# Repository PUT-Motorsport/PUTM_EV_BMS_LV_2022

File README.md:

# PUTM_EV_BMS_LV

## About
Battery Management System (BMS) is an electronic system that manages a rechargeable battery. In case of this project, it will be battery made of 21700 cells packed in 6S2P configuration.

## Tasks of Battery Management System:
- Voltage Measurement on every cell
- Current Measurement
- Temperature Measurement
- State of Charge calculate
- Charge Management with Cell Balance System
- Error Handling based on FSG Rules
- CAN - CAR communication
- Serial data print through USB

## Block diagram of the firmware

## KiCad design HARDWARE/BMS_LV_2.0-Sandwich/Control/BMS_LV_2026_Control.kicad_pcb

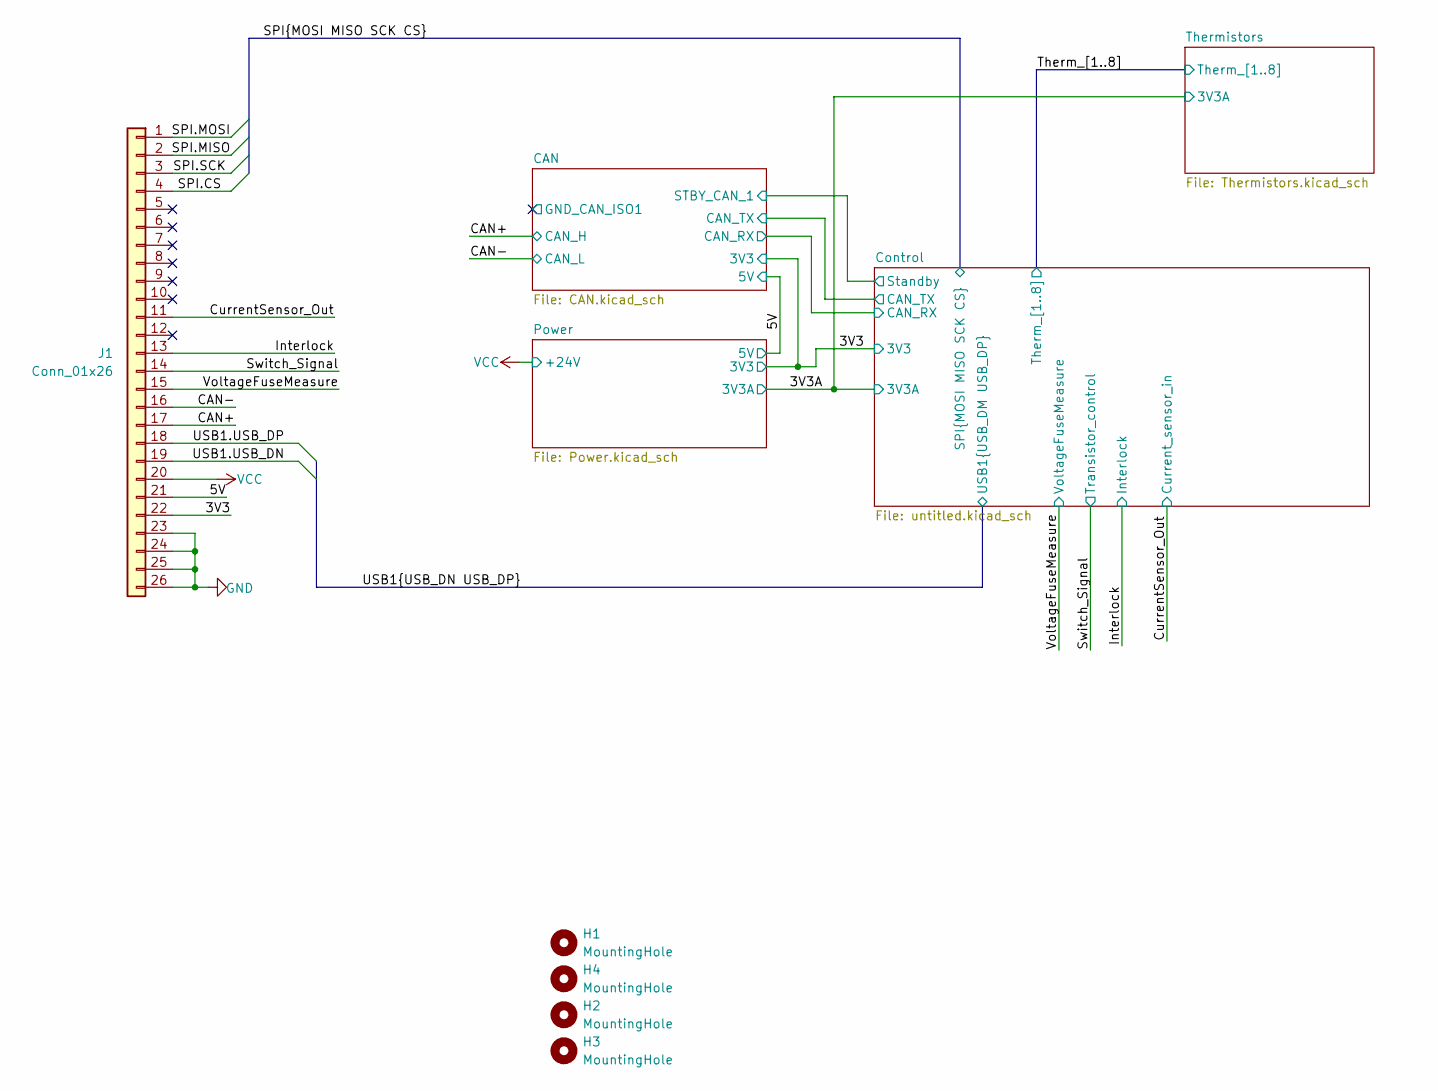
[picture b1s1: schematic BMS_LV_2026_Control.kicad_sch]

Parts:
H1, H2, H3, H4: MountingHole; MountingHole_2.2mm_M2
J1: Conn_01x26; M557002642R; Mouser Part Number M55-6002642R

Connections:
/3V3: J1.22; also elsewhere on the board
/5V: J1.21; also elsewhere on the board
/CAN+: J1.17; also elsewhere on the board
/CAN-: J1.16; also elsewhere on the board
/CurrentSensor_Out: J1.11; also elsewhere on the board
/Interlock: J1.13; also elsewhere on the board
/SPI.CS: J1.4; also elsewhere on the board
/SPI.MISO: J1.2; also elsewhere on the board
/SPI.MOSI: J1.1; also elsewhere on the board
/SPI.SCK: J1.3; also elsewhere on the board
/Switch_Signal: J1.14; also elsewhere on the board
/USB1.USB_DN: J1.19; also elsewhere on the board
/USB1.USB_DP: J1.18; also elsewhere on the board
/VoltageFuseMeasure: J1.15; also elsewhere on the board
GND: J1.23, J1.24, J1.25, J1.26; also elsewhere on the board
VCC: J1.20; also elsewhere on the board

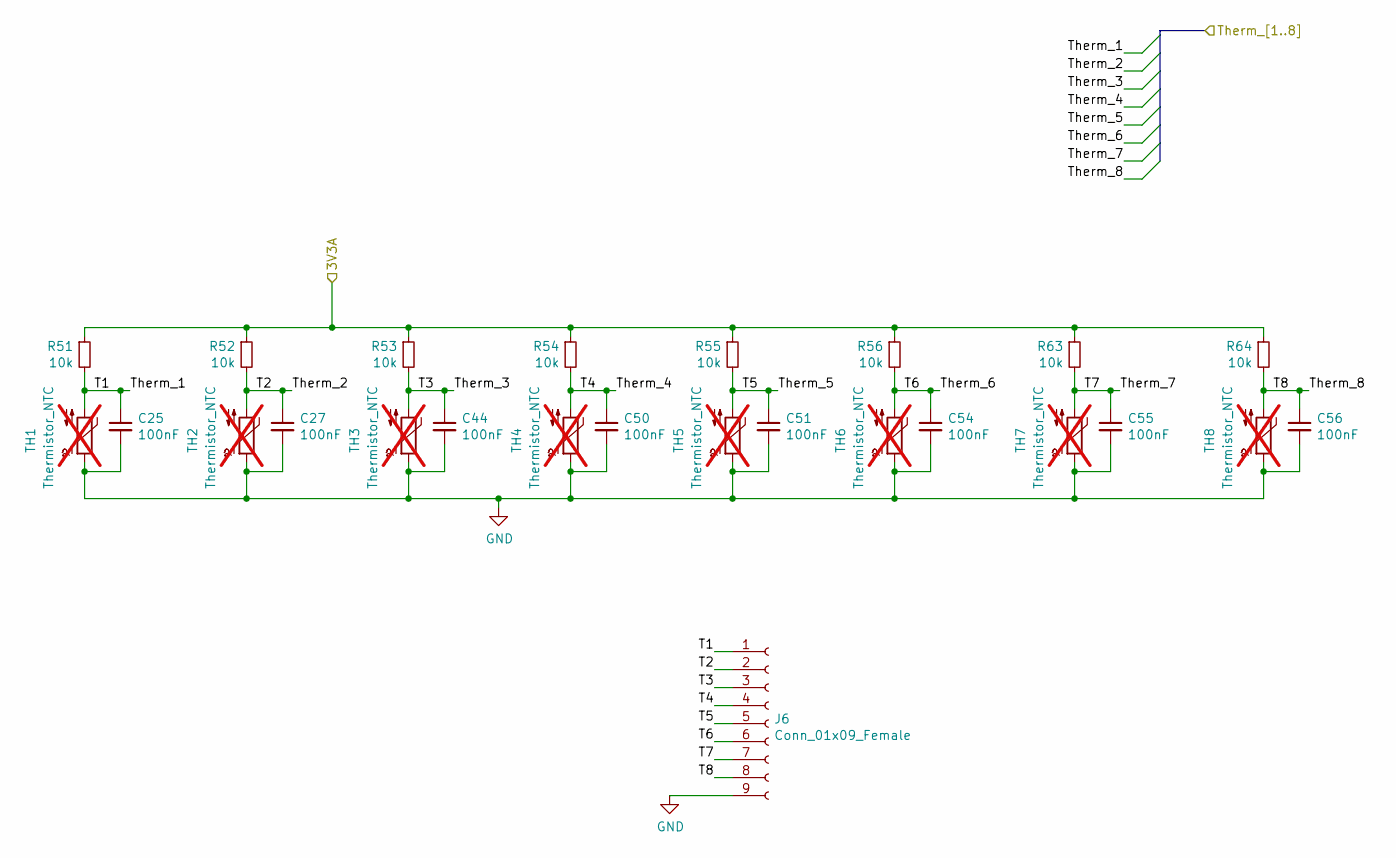
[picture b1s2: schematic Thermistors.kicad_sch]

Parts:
C25, C27, C44, C50, C51, C54, C55, C56: 100nF; C_0603_1608Metric
J6: Conn_01x09_Female; S9BXHA1LFSN
R51, R52, R53, R54, R55, R56, R63, R64: 10k; R_0603_1608Metric
TH1, TH2, TH3, TH4, TH5, TH6, TH7, TH8: Thermistor_NTC; not fitted

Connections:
/3V3A: R51.1, R52.1, R53.1, R54.1, R55.1, R56.1, R63.1, R64.1; also elsewhere on the board
/Therm_1: C25.1, J6.1, R51.2, TH1.2; also elsewhere on the board
/Therm_2: C27.1, J6.2, R52.2, TH2.2; also elsewhere on the board
/Therm_3: C44.1, J6.3, R53.2, TH3.2; also elsewhere on the board
/Therm_4: C50.1, J6.4, R54.2, TH4.2; also elsewhere on the board
/Therm_5: C51.1, J6.5, R55.2, TH5.2; also elsewhere on the board
/Therm_6: C54.1, J6.6, R56.2, TH6.2; also elsewhere on the board
/Therm_7: C55.1, J6.7, R63.2, TH7.2; also elsewhere on the board
/Therm_8: C56.1, J6.8, R64.2, TH8.2; also elsewhere on the board
GND: C25.2, C27.2, C44.2, C50.2, C51.2, C54.2, C55.2, C56.2, J6.9, TH1.1, TH2.1, TH3.1, TH4.1, TH5.1, TH6.1, TH7.1, TH8.1; also elsewhere on the board

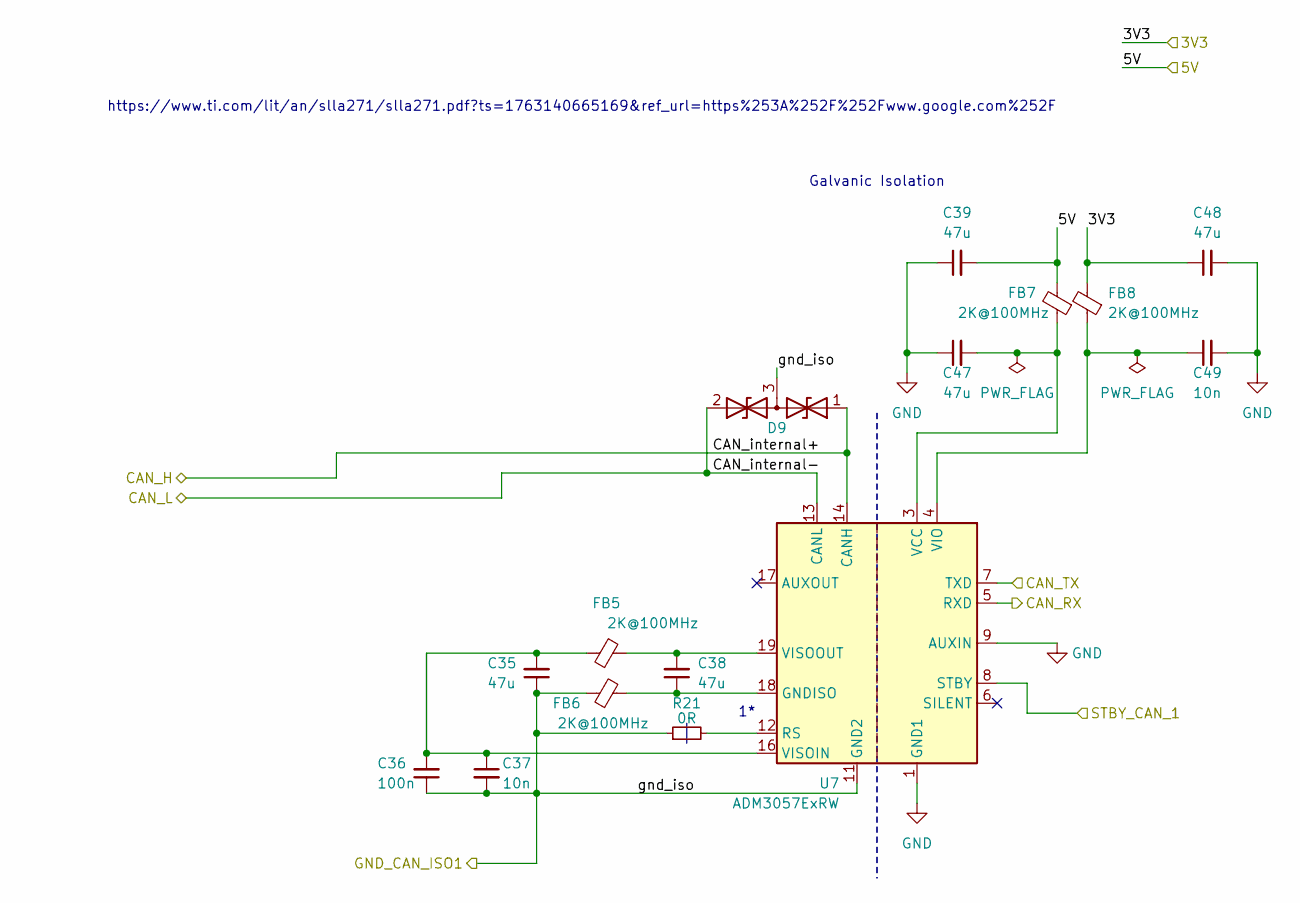
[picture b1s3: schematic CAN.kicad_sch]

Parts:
C35, C38, C39, C47, C48: 47u; C_0805_2012Metric_Pad1.18x1.45mm_HandSolder
C36: 100n; C_0603_1608Metric_Pad1.08x0.95mm_HandSolder
C37, C49: 10n; C_0603_1608Metric_Pad1.08x0.95mm_HandSolder
D9: D_TVS_Dual_AAC; SOT-23_Handsoldering
FB5, FB6, FB7, FB8: 2K@100MHz; L_0805_2012Metric_Pad1.05x1.20mm_HandSolder
R21: 0R; R_0603_1608Metric_Pad0.98x0.95mm_HandSolder
U7: ADM3057ExRW; SOIC-20W_7.5x12.8mm_P1.27mm

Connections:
/3V3: C48.1, FB8.2; also elsewhere on the board
/5V: C39.2, FB7.2; also elsewhere on the board
/CAN+: D9.1 (A1), U7.14 (CANH); also elsewhere on the board
/CAN-: D9.2 (A2), U7.13 (CANL); also elsewhere on the board
/CAN/CAN_RX: U7.5 (RXD); also elsewhere on the board
/CAN/CAN_TX: U7.7 (TXD); also elsewhere on the board
/CAN/STBY_CAN_1: U7.8 (STBY); also elsewhere on the board
/CAN/gnd_iso: C35.1, C36.1, C37.2, D9.3 (common), FB6.1, R21.1, U7.11 (GND2), U7.15 (GND2)
GND: C39.1, C47.1, C48.2, C49.2, U7.1 (GND1), U7.2 (GND1), U7.9 (AUXIN), U7.10 (GND1); also elsewhere on the board
unnamed: C38.1, FB6.2, U7.18 (GNDISO), U7.20 (GNDISO)
unnamed: R21.2, U7.12 (RS)
unnamed: C47.2, FB7.1, U7.3 (VCC)
unnamed: C49.1, FB8.1, U7.4 (VIO)
unnamed: C35.2, C36.2, C37.1, FB5.1, U7.16 (VISOIN)
unnamed: C38.2, FB5.2, U7.19 (VISOOUT)

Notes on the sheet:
https://www.ti.com/lit/an/slla271/slla271.pdf?ts=1763140665169&ref_url=https%253A%252F%252Fwww.google.com%252F
Galvanic Isolation

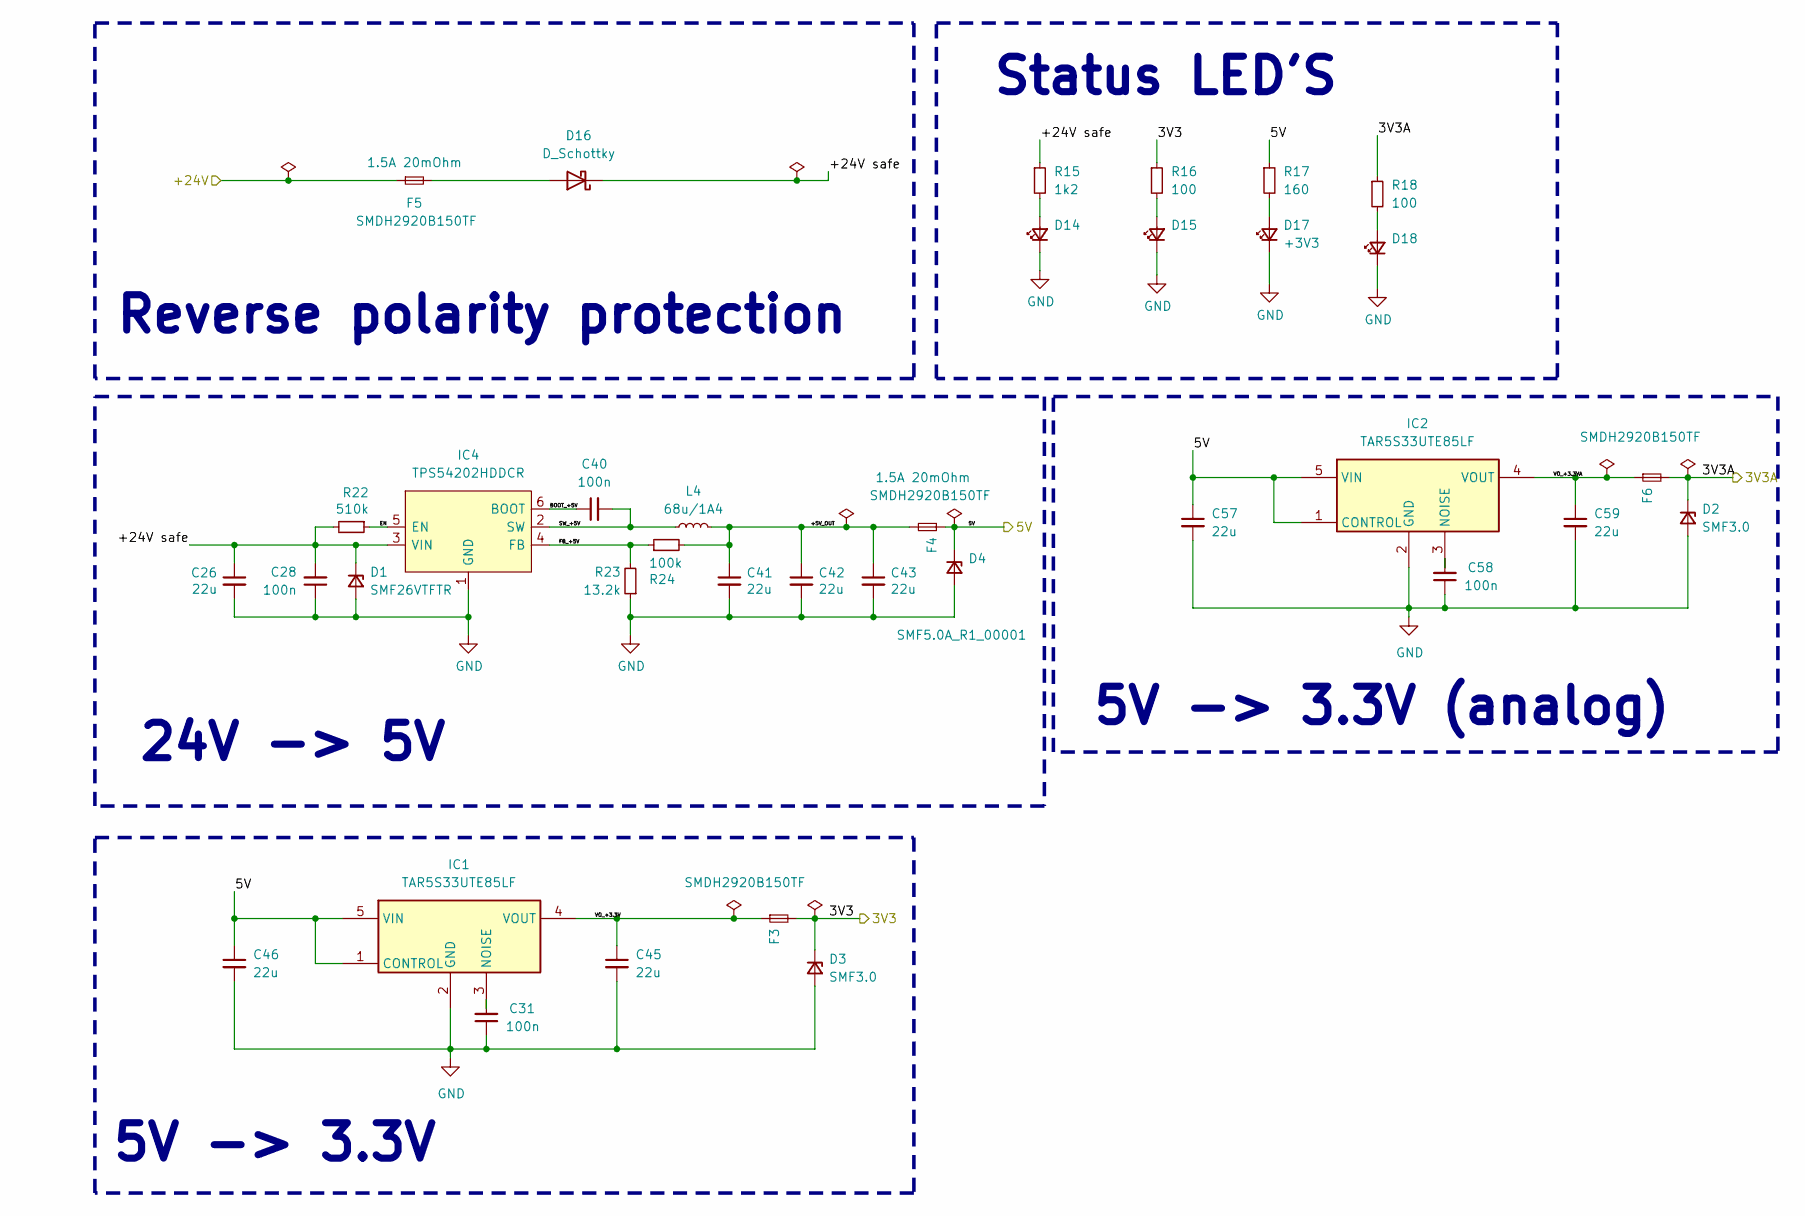
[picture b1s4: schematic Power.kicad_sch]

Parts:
C26, C41, C42, C43: 22u; C_0805_2012Metric_Pad1.18x1.45mm_HandSolder; Manufacturer_Part_Number CL21A107MQYNNWE; Mouser Part Number 810-C2012X5R1V226MAC
C28: 100n; C_0603_1608Metric_Pad1.08x0.95mm_HandSolder; Manufacturer_Part_Number C0603C104J3RACTU; Mouser Part Number 80-C0603C104J3R
C31, C58: 100n; C_0603_1608Metric; Manufacturer_Part_Number C0603C104J3RACTU; Mouser Part Number 80-C0603C104J3R
C40: 100n; C_0603_1608Metric_Pad1.08x0.95mm_HandSolder
C45, C46, C57, C59: 22u; C_0805_2012Metric_Pad1.18x1.45mm_HandSolder
D1: SMF26VTFTR; D_SOD-123F
D2, D3: SMF3.0; D_SOD-123F
D4: SMF5.0A_R1_00001; D_SOD-123F
D14, D15, D18: LED_0603_1608Metric_Pad1.05x0.95mm_HandSolder
D16: D_Schottky; D_0603_1608Metric_Pad1.05x0.95mm_HandSolder
D17: +3V3; LED_0603_1608Metric_Pad1.05x0.95mm_HandSolder
F3, F4, F5, F6: SMDH2920B150TF; Fuse_2920_7451Metric_Pad2.10x5.45mm_HandSolder
IC1, IC2: TAR5S33UTE85LF; SOTFL65P210X75-5N; Mouser Part Number 757-TAR5S33UTE85LF
IC4: TPS54202HDDCR; SOT-23-6_Handsoldering; Mouser Part Number 595-TPS54202HDDCR
L4: 68u/1A4; L_Vishay_IFSC-1515AH_4x4x1.8mm; Mouser Part Number 810-VLS6045EX-680M
R15: 1k2; R_0603_1608Metric_Pad0.98x0.95mm_HandSolder
R16, R18: 100; R_0603_1608Metric_Pad0.98x0.95mm_HandSolder
R17: 160; R_0603_1608Metric_Pad0.98x0.95mm_HandSolder
R22: 510k; R_0603_1608Metric_Pad0.98x0.95mm_HandSolder; Manufacturer_Part_Number RT0603DRD07510KL; Mouser Part Number 603-RT0603DRD07510KL
R23: 13.2k; R_0603_1608Metric_Pad0.98x0.95mm_HandSolder; Manufacturer_Part_Number RT0603DRE0713K3L; Mouser Part Number 603-RT0603DRE0713K3L
R24: 100k; R_0603_1608Metric_Pad0.98x0.95mm_HandSolder; Manufacturer_Part_Number RT0603DRE07100KL; Mouser Part Number 603-RT0603DRE07100KL

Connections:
/3V3: D3.1 (K), F3.2, R16.1; also elsewhere on the board
/3V3A: D2.1 (K), F6.2, R18.1; also elsewhere on the board
/5V: C46.1, C57.1, D4.1 (K), F4.1, IC1.1 (CONTROL), IC1.5 (VIN), IC2.1 (CONTROL), IC2.5 (VIN), R17.1; also elsewhere on the board
/Power/+5V_OUT: C41.1, C42.1, C43.1, F4.2, L4.2, R24.2
/Power/+24V safe: C26.1, C28.2, D1.1 (K), D16.1 (K), IC4.3 (VIN), R15.1, R22.2
/Power/BOOT_+5V: C40.1, IC4.6 (BOOT)
/Power/EN: IC4.5 (EN), R22.1
/Power/FB_+5V: IC4.4 (FB), R23.2, R24.1
/Power/SW_+5V: C40.2, IC4.2 (SW), L4.1
/Power/VO_+3.3V: C45.1, F3.1, IC1.4 (VOUT)
/Power/VO_+3.3VA: C59.1, F6.1, IC2.4 (VOUT)
GND: C26.2, C28.1, C31.1, C41.2, C42.2, C43.2, C45.2, C46.2, C57.2, C58.1, C59.2, D1.2 (A), D2.2 (A), D3.2 (A), D4.2 (A), D14.1 (K), D15.1 (K), D17.1 (K), D18.1 (K), IC1.2 (GND), IC2.2 (GND), IC4.1 (GND), R23.1; also elsewhere on the board
unnamed: D14.2 (A), R15.2
unnamed: D15.2 (A), R16.2
unnamed: D16.2 (A), F5.2
unnamed: D17.2 (A), R17.2
unnamed: D18.2 (A), R18.2
unnamed: C31.2, IC1.3 (NOISE)
unnamed: C58.2, IC2.3 (NOISE)
VCC: F5.1; also elsewhere on the board

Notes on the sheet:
Status LED'S
5V -> 3.3V (analog)
Reverse polarity protection
24V -> 5V
5V -> 3.3V

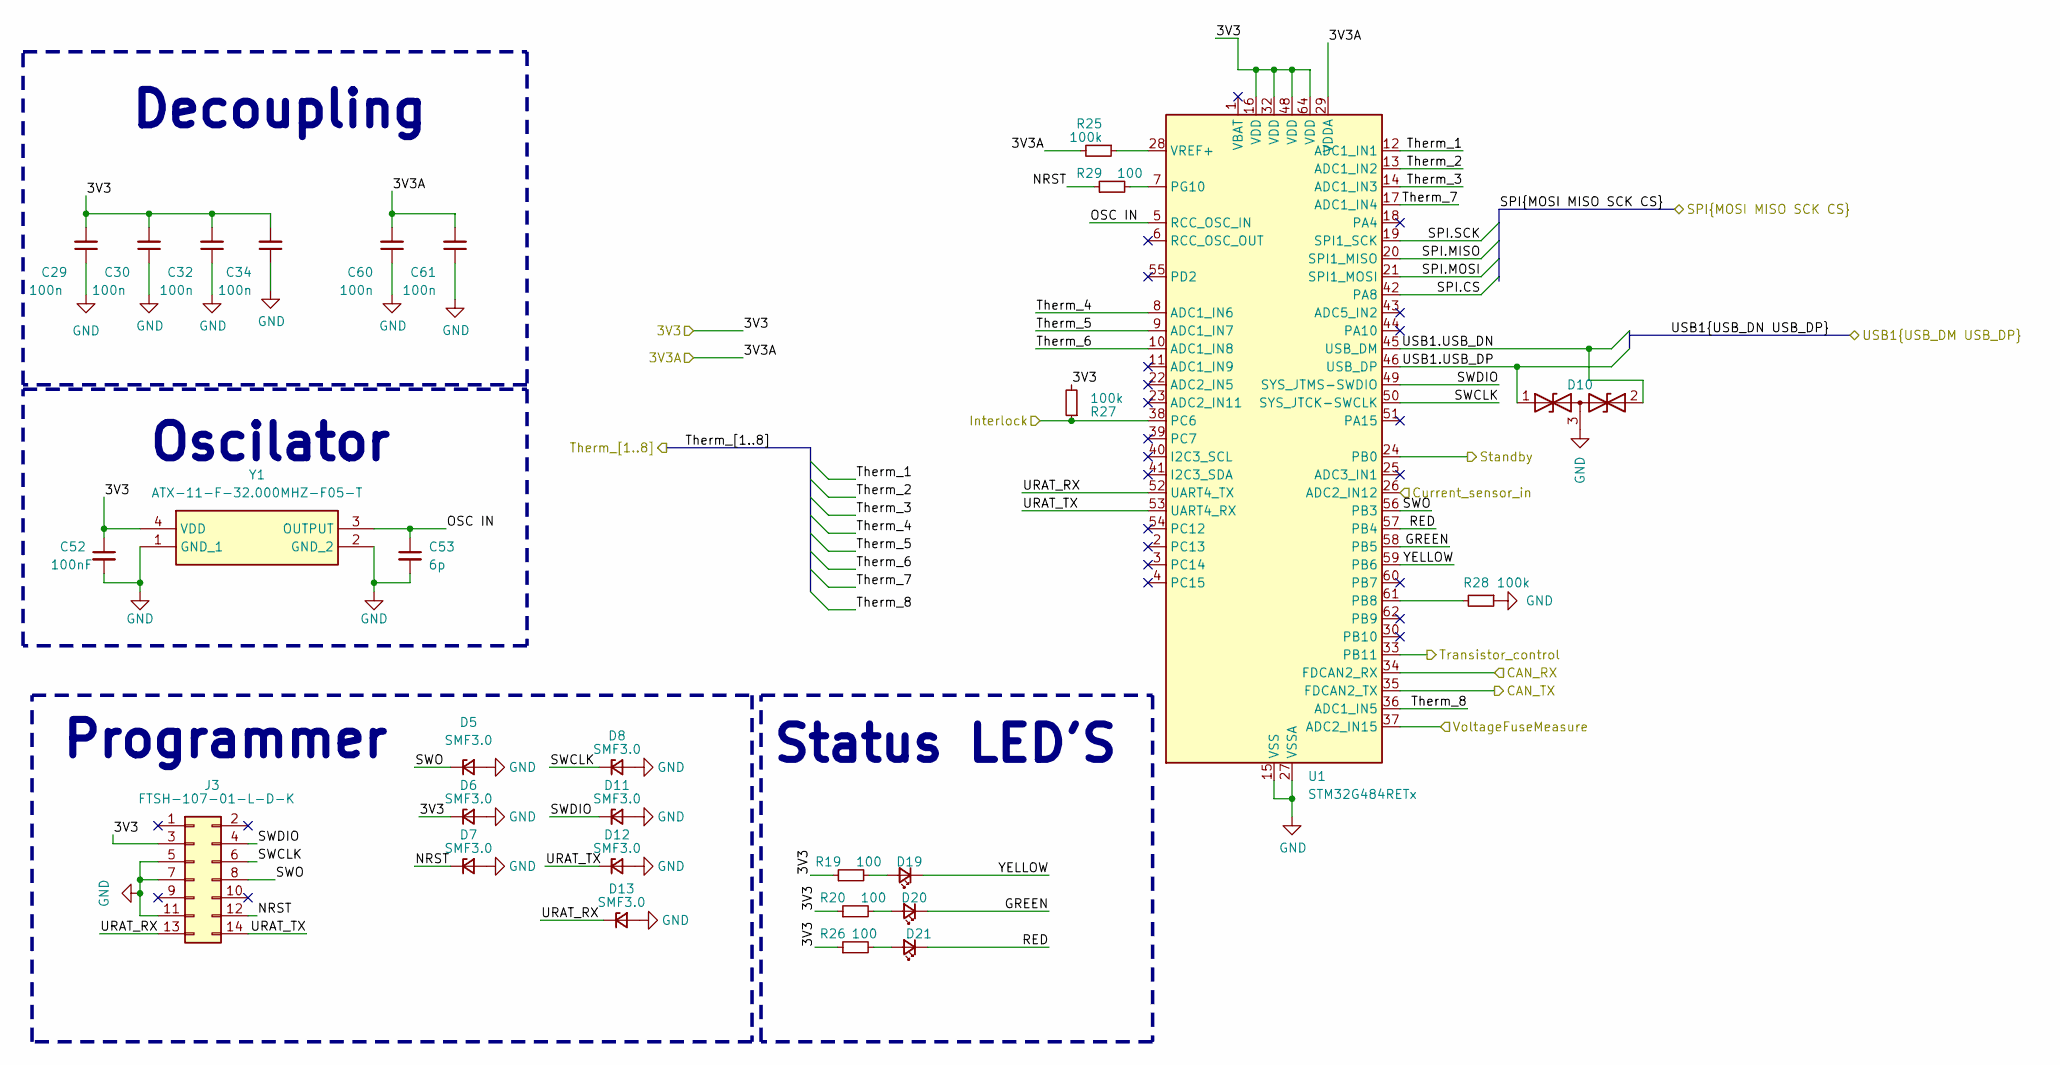
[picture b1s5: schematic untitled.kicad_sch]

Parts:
C29, C30, C32, C34, C60, C61: 100n; C_0603_1608Metric_Pad1.08x0.95mm_HandSolder; Manufacturer_Part_Number C0603C104J3RACTU; Mouser Part Number 80-C0603C104J3R
C52: 100nF; C_0603_1608Metric_Pad1.08x0.95mm_HandSolder
C53: 6p; C_0603_1608Metric_Pad1.08x0.95mm_HandSolder
D5, D6, D7, D8, D11, D12, D13: SMF3.0; D_SOD-123F
D10: D_TVS_Dual_AAC; SOT-23_Handsoldering
D19, D20, D21: LED_0603_1608Metric_Pad1.05x0.95mm_HandSolder
J3: FTSH-107-01-L-D-K; FTSH-107-XX-YYY-DH-TR; Mouser Part Number 200-FTSH10701LDK
R19, R20, R26, R29: 100; R_0603_1608Metric_Pad0.98x0.95mm_HandSolder
R25, R28: 100k; R_0603_1608Metric_Pad0.98x0.95mm_HandSolder
R27: 100k; R_0603_1608Metric_Pad0.98x0.95mm_HandSolder; Manufacturer_Part_Number RT0603DRE07100KL; Mouser Part Number 603-RT0603DRE07100KL
U1: STM32G484RETx; LQFP-64_10x10mm_P0.5mm
Y1: ATX-11-F-32.000MHZ-F05-T; ATX11F32000MHZF05T; Mouser Part Number 815-ATX11F32000MF05T

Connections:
/3V3: C29.2, C30.2, C32.2, C34.2, C52.1, D6.1 (K), J3.3, R19.1, R20.1, R26.1, R27.2, U1.16 (VDD), U1.32 (VDD), U1.48 (VDD), U1.64 (VDD), Y1.4 (VDD); also elsewhere on the board
/3V3A: C60.2, C61.2, R25.2, U1.29 (VDDA); also elsewhere on the board
/CAN/CAN_RX: U1.34 (FDCAN2_RX); also elsewhere on the board
/CAN/CAN_TX: U1.35 (FDCAN2_TX); also elsewhere on the board
/CAN/STBY_CAN_1: U1.24 (PB0); also elsewhere on the board
/Control/GREEN: D20.1 (K), U1.58 (PB5)
/Control/NRST: D7.1 (K), J3.12, R29.1
/Control/OSC IN: C53.1, U1.5 (RCC_OSC_IN), Y1.3 (OUTPUT)
/Control/RED: D21.1 (K), U1.57 (PB4)
/Control/SWCLK: D8.1 (K), J3.6, U1.50 (SYS_JTCK-SWCLK)
/Control/SWDIO: D11.1 (K), J3.4, U1.49 (SYS_JTMS-SWDIO)
/Control/SWO: D5.1 (K), J3.8, U1.56 (PB3)
/Control/URAT_RX: D13.1 (K), J3.13, U1.52 (UART4_TX)
/Control/URAT_TX: D12.1 (K), J3.14, U1.53 (UART4_RX)
/Control/YELLOW: D19.1 (K), U1.59 (PB6)
/CurrentSensor_Out: U1.26 (ADC2_IN12); also elsewhere on the board
/Interlock: R27.1, U1.38 (PC6); also elsewhere on the board
/SPI.CS: U1.42 (PA8); also elsewhere on the board
/SPI.MISO: U1.20 (SPI1_MISO); also elsewhere on the board
/SPI.MOSI: U1.21 (SPI1_MOSI); also elsewhere on the board
/SPI.SCK: U1.19 (SPI1_SCK); also elsewhere on the board
/Switch_Signal: U1.33 (PB11); also elsewhere on the board
/Therm_1: U1.12 (ADC1_IN1); also elsewhere on the board
/Therm_2: U1.13 (ADC1_IN2); also elsewhere on the board
/Therm_3: U1.14 (ADC1_IN3); also elsewhere on the board
/Therm_4: U1.8 (ADC1_IN6); also elsewhere on the board
/Therm_5: U1.9 (ADC1_IN7); also elsewhere on the board
/Therm_6: U1.10 (ADC1_IN8); also elsewhere on the board
/Therm_7: U1.17 (ADC1_IN4); also elsewhere on the board
/Therm_8: U1.36 (ADC1_IN5); also elsewhere on the board
/USB1.USB_DN: D10.2 (A2), U1.45 (USB_DM); also elsewhere on the board
/USB1.USB_DP: D10.1 (A1), U1.46 (USB_DP); also elsewhere on the board
/VoltageFuseMeasure: U1.37 (ADC2_IN15); also elsewhere on the board
GND: C29.1, C30.1, C32.1, C34.1, C52.2, C53.2, C60.1, C61.1, D5.2 (A), D6.2 (A), D7.2 (A), D8.2 (A), D10.3 (common), D11.2 (A), D12.2 (A), D13.2 (A), J3.5, J3.7, J3.11, R28.1, U1.15 (VSS), U1.27 (VSSA), U1.31 (VSS), U1.47 (VSS), U1.63 (VSS), Y1.1 (GND_1), Y1.2 (GND_2); also elsewhere on the board
unnamed: D19.2 (A), R19.2
unnamed: D20.2 (A), R20.2
unnamed: D21.2 (A), R26.2
unnamed: R28.2, U1.61 (PB8)
unnamed: R29.2, U1.7 (PG10)
unnamed: R25.1, U1.28 (VREF+)

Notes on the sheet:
Decoupling
Status LED'S
Oscilator
Programmer

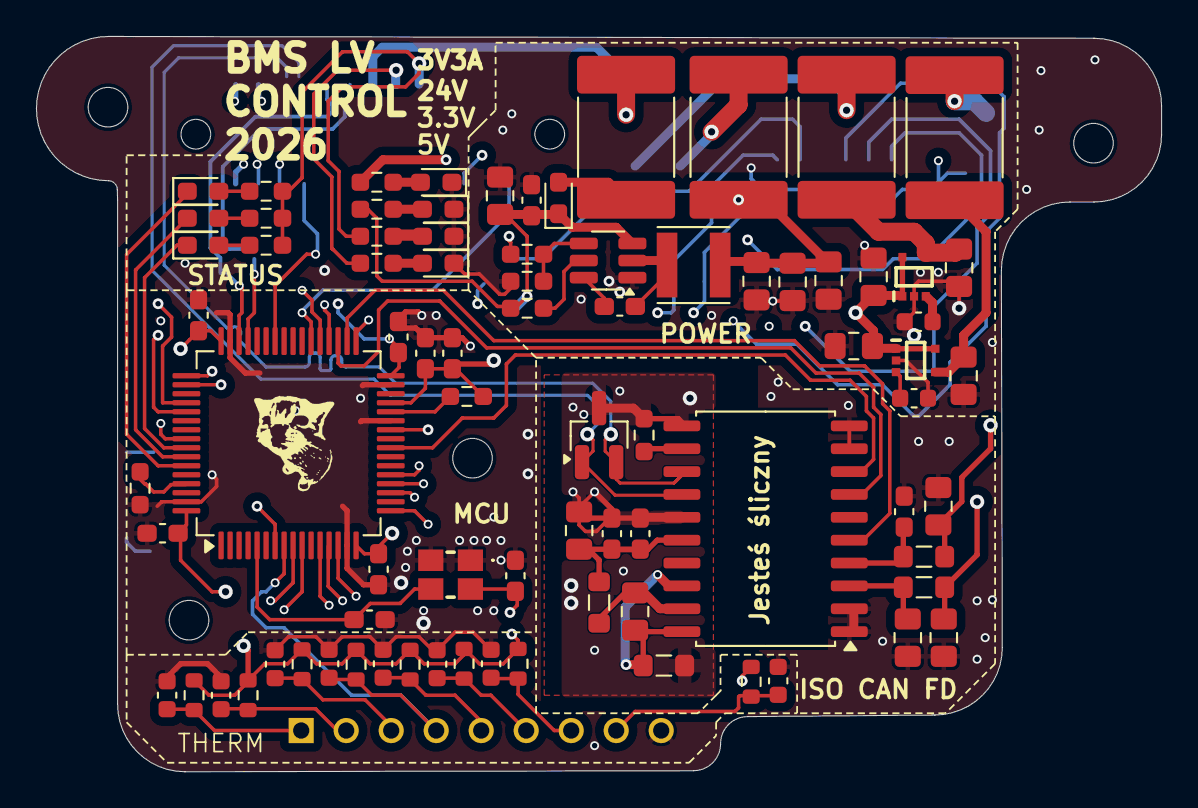
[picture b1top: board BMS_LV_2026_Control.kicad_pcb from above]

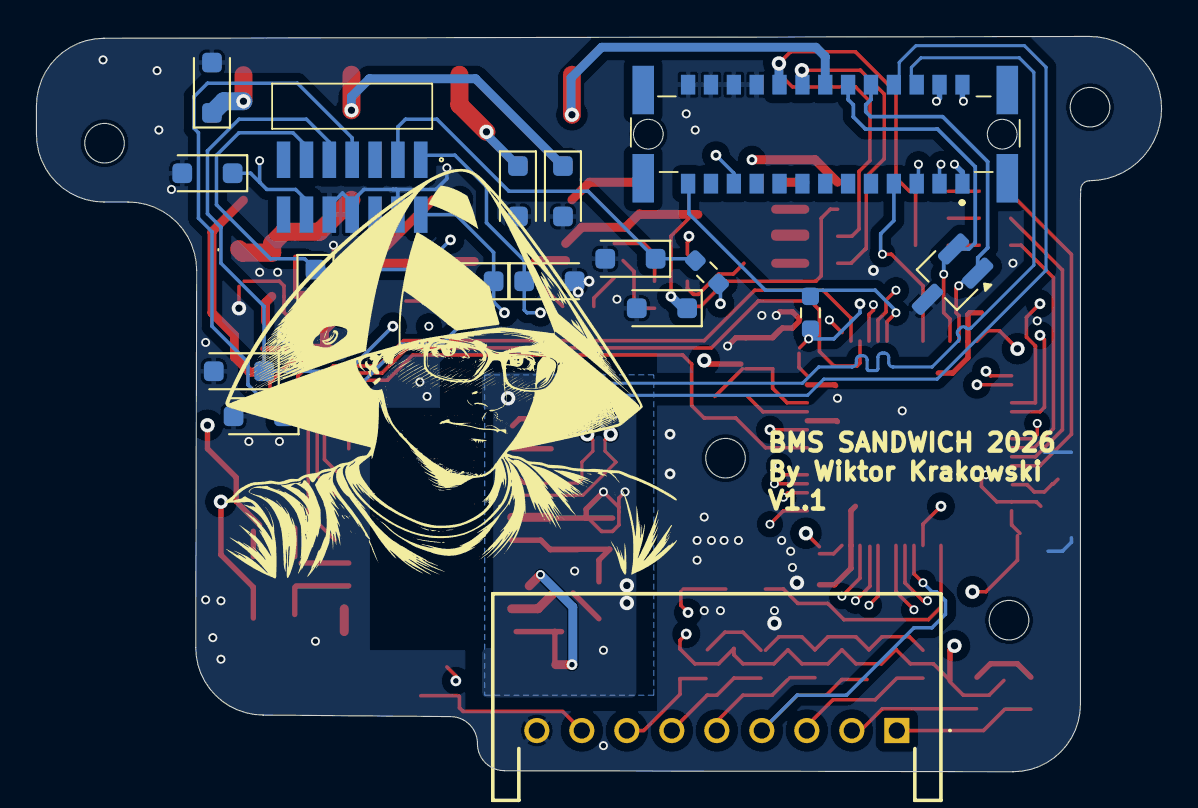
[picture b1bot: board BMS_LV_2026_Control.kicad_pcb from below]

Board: 6 copper layers, 62.5 x 40.8 mm, 102 parts (17 on the bottom side), 66 nets.

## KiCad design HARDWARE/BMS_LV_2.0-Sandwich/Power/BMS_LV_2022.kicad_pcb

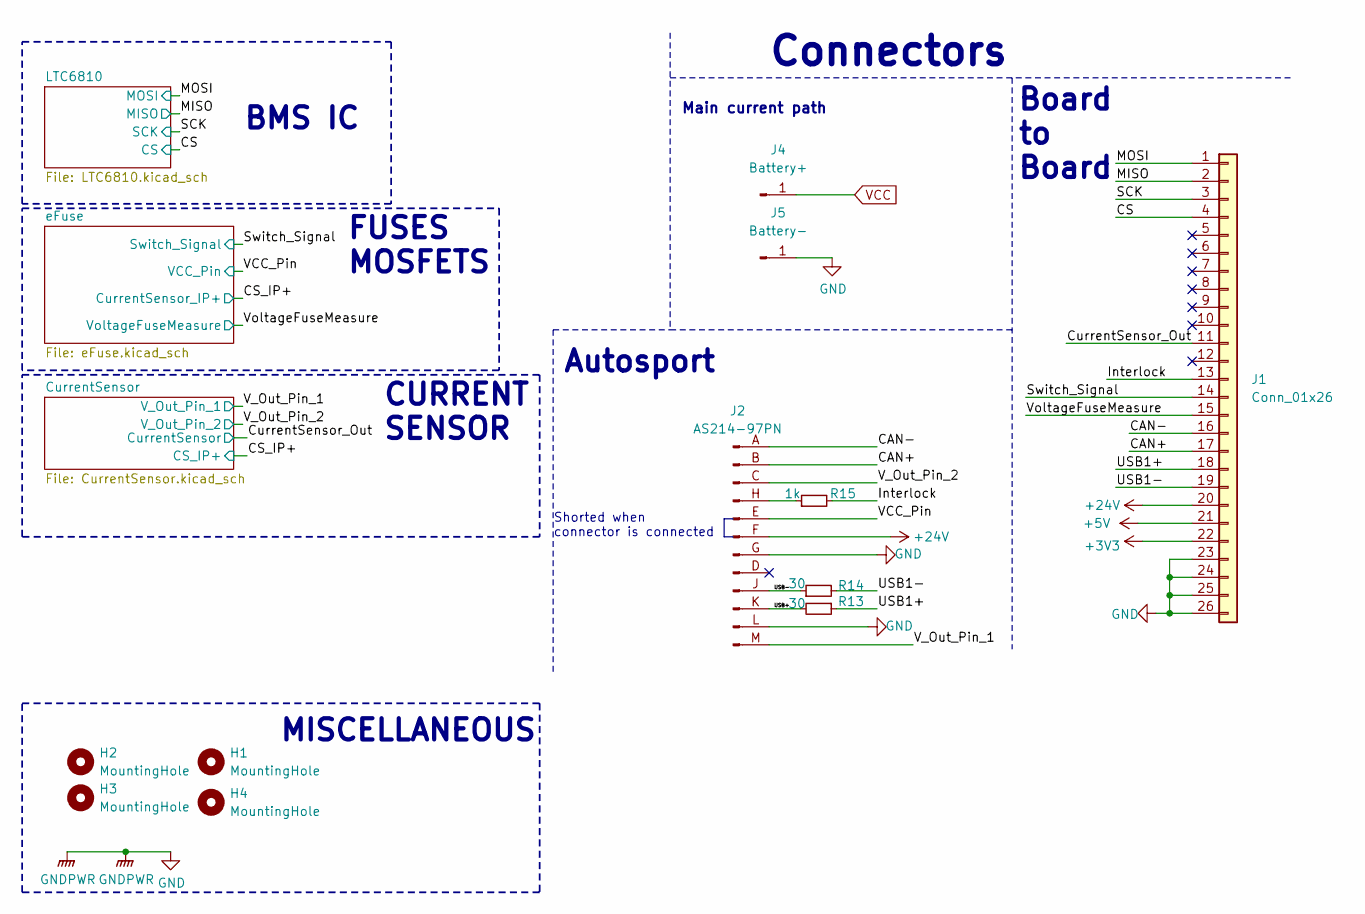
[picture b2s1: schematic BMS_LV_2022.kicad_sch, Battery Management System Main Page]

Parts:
H1, H2, H3, H4: MountingHole; MountingHole_2.2mm_M2
J1: Conn_01x26; M556002642R; Mouser Part Number M55-6002642R
J2: AS214-97PN
J4: Battery+; CellPad
J5: Battery-; CellPad
R13, R14: 30; R_0603_1608Metric
R15: 1k; R_0603_1608Metric

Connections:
+3V3: J1.22
+5V: J1.21; also elsewhere on the board
+24V: J1.20, J2.F
/CAN+: J1.17, J2.B
/CAN-: J1.16, J2.A
/CS: J1.4; also elsewhere on the board
/CurrentSensor_Out: J1.11; also elsewhere on the board
/Interlock: J1.13, R15.2
/MISO: J1.2; also elsewhere on the board
/MOSI: J1.1; also elsewhere on the board
/SCK: J1.3; also elsewhere on the board
/Switch_Signal: J1.14; also elsewhere on the board
/USB1+: J1.18, R13.1
/USB1-: J1.19, R14.2
/USB+: J2.K, R13.2
/USB-: J2.J, R14.1
/VCC_Pin: J2.E; also elsewhere on the board
/V_Out_Pin_1: J2.M; also elsewhere on the board
/V_Out_Pin_2: J2.C; also elsewhere on the board
/VoltageFuseMeasure: J1.15; also elsewhere on the board
GND: J1.23, J1.24, J1.25, J1.26, J2.G, J2.L, J5.1 (Pin_1_1); also elsewhere on the board
unnamed: J2.H, R15.1
VCC: J4.1 (Pin_1_1); also elsewhere on the board

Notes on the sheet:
BMS IC
Main current path
CURRENT SENSOR
Shorted when connector is connected
Connectors
FUSES MOSFETS
Board to Board
MISCELLANEOUS
Autosport

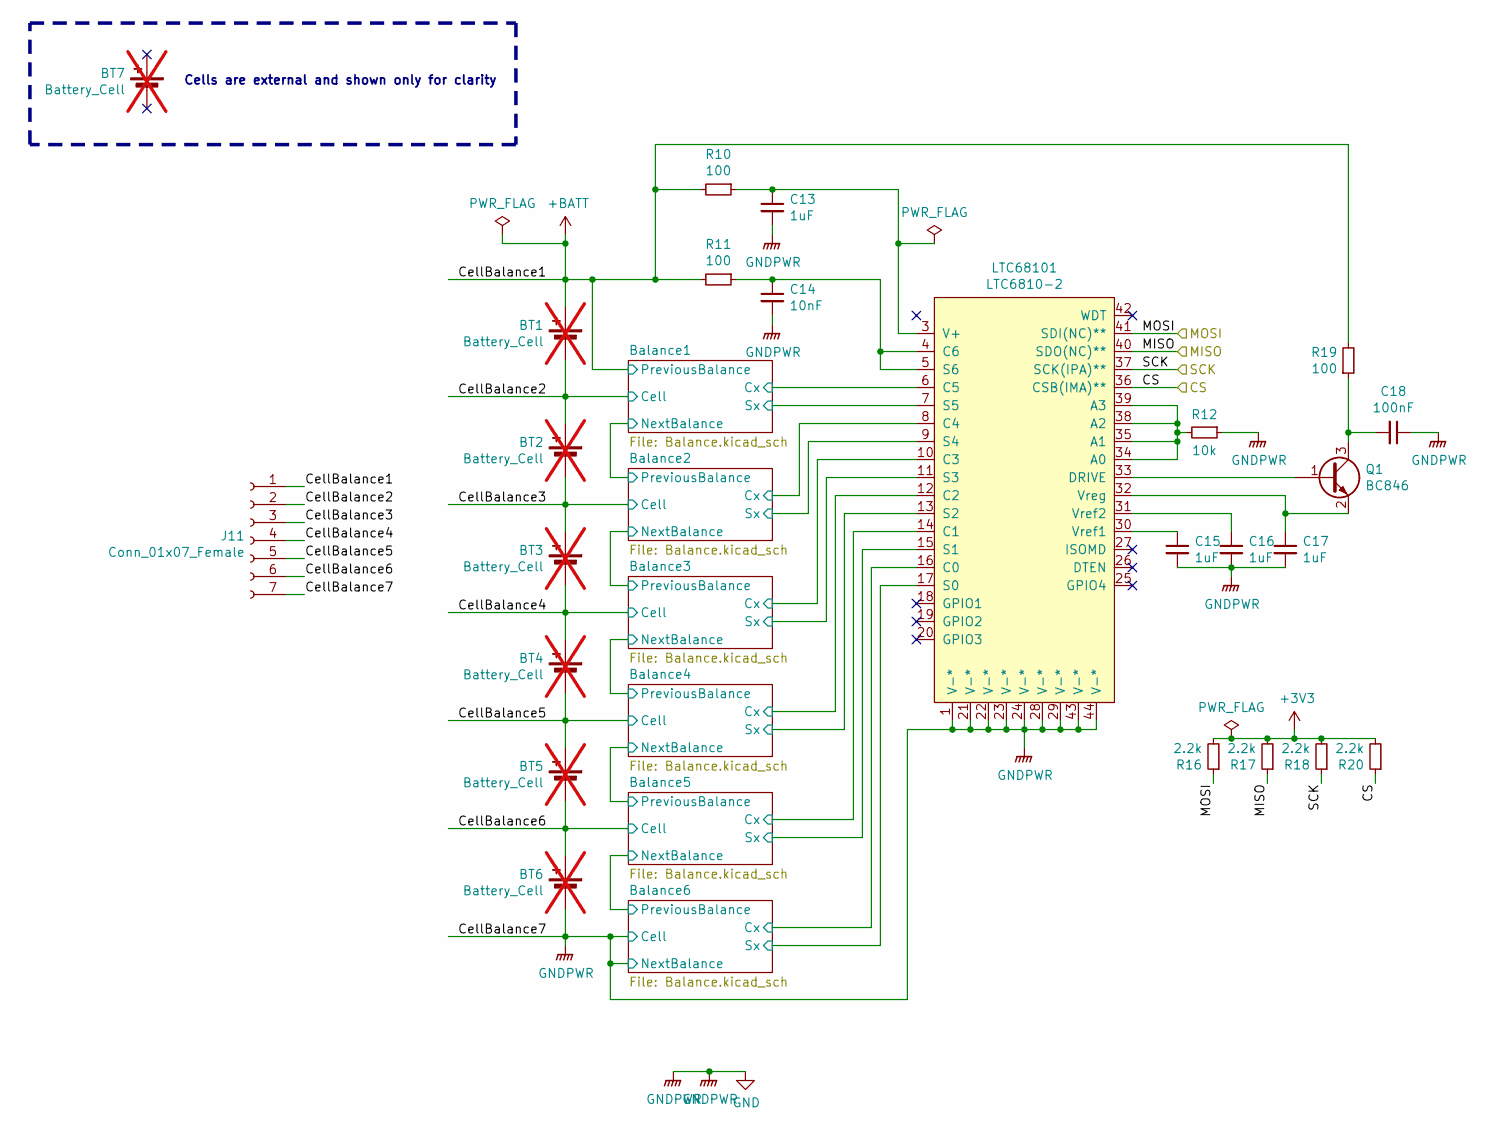
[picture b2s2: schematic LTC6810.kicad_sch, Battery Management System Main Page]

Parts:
BT1, BT2, BT3, BT4, BT5, BT6, BT7: Battery_Cell; not fitted
C13, C15, C16, C17: 1uF; C_0603_1608Metric
C14: 10nF; C_0603_1608Metric
C18: 100nF; C_0603_1608Metric
J11: Conn_01x07_Female; JST_XH_B7B-XH-A_1x07_P2.50mm_Vertical
LTC68101: LTC6810-2; LTC6810
Q1: BC846; SOT-23
R10, R11, R19: 100; R_0603_1608Metric
R12: 10k; R_0603_1608Metric
R16, R17, R18, R20: 2.2k; R_0603_1608Metric

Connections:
+BATT: BT1.1 (+), J11.1, R10.2, R11.2, R19.2; also elsewhere on the board
/CS: LTC68101.36 (CSB(IMA)**), R20.1; also elsewhere on the board
/LTC6810/Balance1/Cx: LTC68101.6 (C5); also elsewhere on the board
/LTC6810/Balance1/Sx: LTC68101.7 (S5); also elsewhere on the board
/LTC6810/Balance2/Cx: LTC68101.8 (C4); also elsewhere on the board
/LTC6810/Balance2/Sx: LTC68101.9 (S4); also elsewhere on the board
/LTC6810/Balance3/Cx: LTC68101.10 (C3); also elsewhere on the board
/LTC6810/Balance3/Sx: LTC68101.11 (S3); also elsewhere on the board
/LTC6810/Balance4/Cx: LTC68101.12 (C2); also elsewhere on the board
/LTC6810/Balance4/Sx: LTC68101.13 (S2); also elsewhere on the board
/LTC6810/Balance5/Cx: LTC68101.14 (C1); also elsewhere on the board
/LTC6810/Balance5/Sx: LTC68101.15 (S1); also elsewhere on the board
/LTC6810/Balance6/Cx: LTC68101.16 (C0); also elsewhere on the board
/LTC6810/Balance6/Sx: LTC68101.17 (S0); also elsewhere on the board
/LTC6810/CellBalance2: BT1.2 (-), BT2.1 (+), J11.2; also elsewhere on the board
/LTC6810/CellBalance3: BT2.2 (-), BT3.1 (+), J11.3; also elsewhere on the board
/LTC6810/CellBalance4: BT3.2 (-), BT4.1 (+), J11.4; also elsewhere on the board
/LTC6810/CellBalance5: BT4.2 (-), BT5.1 (+), J11.5; also elsewhere on the board
/LTC6810/CellBalance6: BT5.2 (-), BT6.1 (+), J11.6; also elsewhere on the board
/MISO: LTC68101.40 (SDO(NC)**), R17.1; also elsewhere on the board
/MOSI: LTC68101.41 (SDI(NC)**), R16.1; also elsewhere on the board
/SCK: LTC68101.37 (SCK(IPA)**), R18.1; also elsewhere on the board
GND: BT6.2 (-), C13.2, C14.2, C15.2, C16.2, C17.2, C18.1, J11.7, LTC68101.1 (V-*), LTC68101.21 (V-*), LTC68101.22 (V-*), LTC68101.23 (V-*), LTC68101.24 (V-*), LTC68101.28 (V-*), LTC68101.29 (V-*), LTC68101.43 (V-*), LTC68101.44 (V-*), R12.1; also elsewhere on the board
unnamed: LTC68101.34 (A0), LTC68101.35 (A1), LTC68101.38 (A2), LTC68101.39 (A3), R12.2
unnamed: C14.1, LTC68101.4 (C6), LTC68101.5 (S6), R11.1
unnamed: LTC68101.33 (DRIVE), Q1.1 (B)
unnamed: C13.1, LTC68101.3 (V+), R10.1
unnamed: C15.1, LTC68101.30 (Vref1)
unnamed: C16.1, LTC68101.31 (Vref2)
unnamed: C17.1, LTC68101.32 (Vreg), Q1.2 (E)
unnamed: C18.2, Q1.3 (C), R19.1
unnamed: R16.2, R17.2, R18.2, R20.2

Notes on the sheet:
Cells are external and shown only for clarity

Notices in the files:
parts and their libraries:
License: Apache-2.0
